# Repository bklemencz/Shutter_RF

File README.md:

STM8S103 mini board based shutter controller

- 433MHz EV1527 based remote control
- RS485 Intarface
- IIC interface and RF transmitter on board
- 2 relays for 3 wire tubular shutter motors
- External switch
- Time based partially open and closed positions

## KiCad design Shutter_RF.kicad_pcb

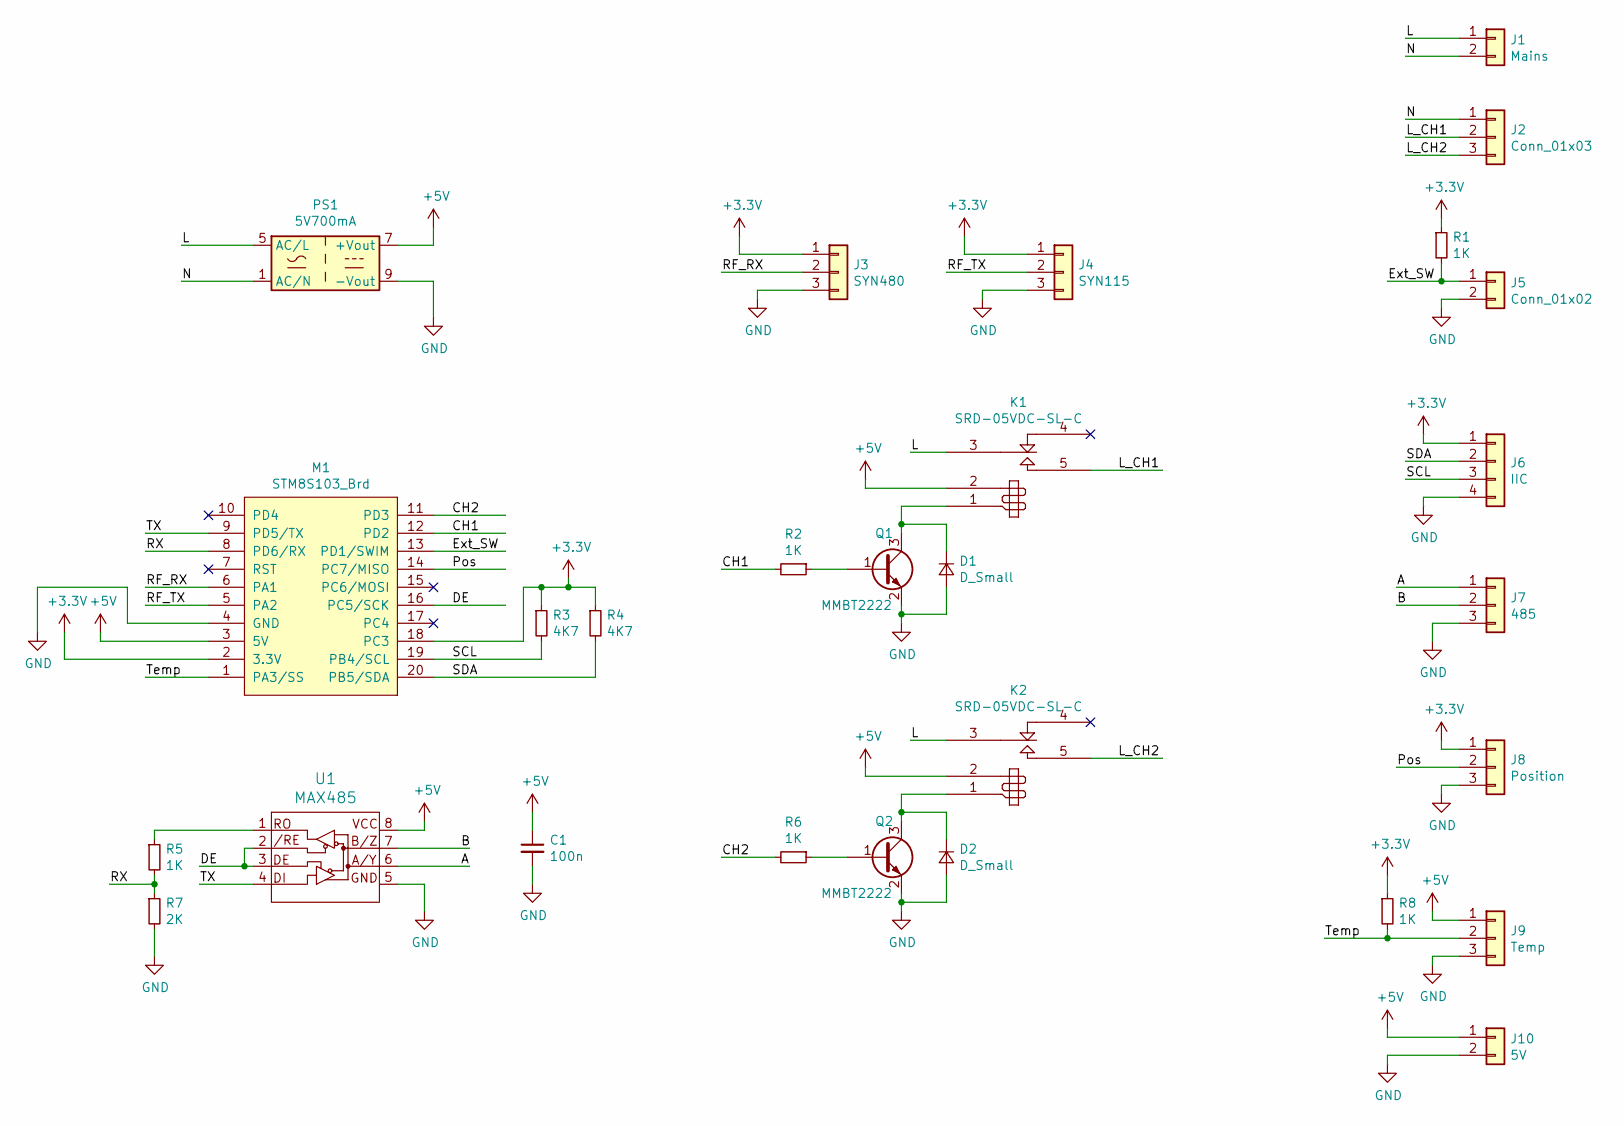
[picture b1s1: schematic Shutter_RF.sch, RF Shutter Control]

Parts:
C1: 100n; C_0805
D1, D2: D_Small; D_SMA
J1: Mains; Screw_Terminal_1x02
J2: Conn_01x03; Screw_Terminal_1x03
J3: SYN480; SYN480R_Mod
J4: SYN115; SYN115_Mod
J5: Conn_01x02; Screw_Terminal_1x02
J6: IIC; JST_PH_B4B-PH-K_04x2.00mm_Straight
J7: 485; JST_PH_B3B-PH-K_03x2.00mm_Straight
J8: Position; JST_PH_B3B-PH-K_03x2.00mm_Straight
J9: Temp; JST_PH_B3B-PH-K_03x2.00mm_Straight
J10: 5V; Screw_Terminal_1x02
K1, K2: SRD-05VDC-SL-C; REY5-19.0X15.0X15.0MM
M1: STM8S103_Brd; STM8S103_Minimum_Board
PS1: 5V700mA; 5V700mA_ACDC
Q1, Q2: MMBT2222; SOT-23
R1, R2, R5, R6, R8: 1K; R_0805
R3, R4: 4K7; R_0805
R7: 2K; R_0805
U1: MAX485; SOIC-8_3.9x4.9mm_Pitch1.27mm

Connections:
+3V3: J3.1, J4.1, J6.1, J8.1, M1.2 (3.3V), M1.18 (PC3), R1.1, R3.1, R4.1, R8.1
+5V: C1.1, J9.1, J10.1, K1.2, K2.2, M1.3 (5V), PS1.7 (+Vout), U1.8 (VCC)
/A: J7.1, U1.6 (A/Y)
/B: J7.2, U1.7 (B/Z)
/CH1: M1.12 (PD2), R2.2
/CH2: M1.11 (PD3), R6.2
/DE: M1.16 (PC5/SCK), U1.2 (/RE), U1.3 (DE)
/Ext_SW: J5.1, M1.13 (PD1/SWIM), R1.2
/L: J1.1, K1.3, K2.3, PS1.5 (AC/L)
/L_CH1: J2.2, K1.5
/L_CH2: J2.3, K2.5
/N: J1.2, J2.1, PS1.1 (AC/N)
/Pos: J8.2, M1.14 (PC7/MISO)
/RF_RX: J3.2, M1.6 (PA1)
/RF_TX: J4.2, M1.5 (PA2)
/RX: M1.8 (PD6/RX), R5.2, R7.1
/SCL: J6.3, M1.19 (PB4/SCL), R3.2
/SDA: J6.2, M1.20 (PB5/SDA), R4.2
/TX: M1.9 (PD5/TX), U1.4 (DI)
/Temp: J9.2, M1.1 (PA3/SS), R8.2
GND: C1.2, D1.2 (A), D2.2 (A), J3.3, J4.3, J5.2, J6.4, J7.3, J8.3, J9.3, J10.2, M1.4 (GND), PS1.9 (-Vout), Q1.2 (E), Q2.2 (E), R7.2, U1.5 (GND)
unnamed: D1.1 (K), K1.1, Q1.3 (C)
unnamed: D2.1 (K), K2.1, Q2.3 (C)
unnamed: Q1.1 (B), R2.1
unnamed: Q2.1 (B), R6.1
unnamed: R5.1, U1.1 (RO)

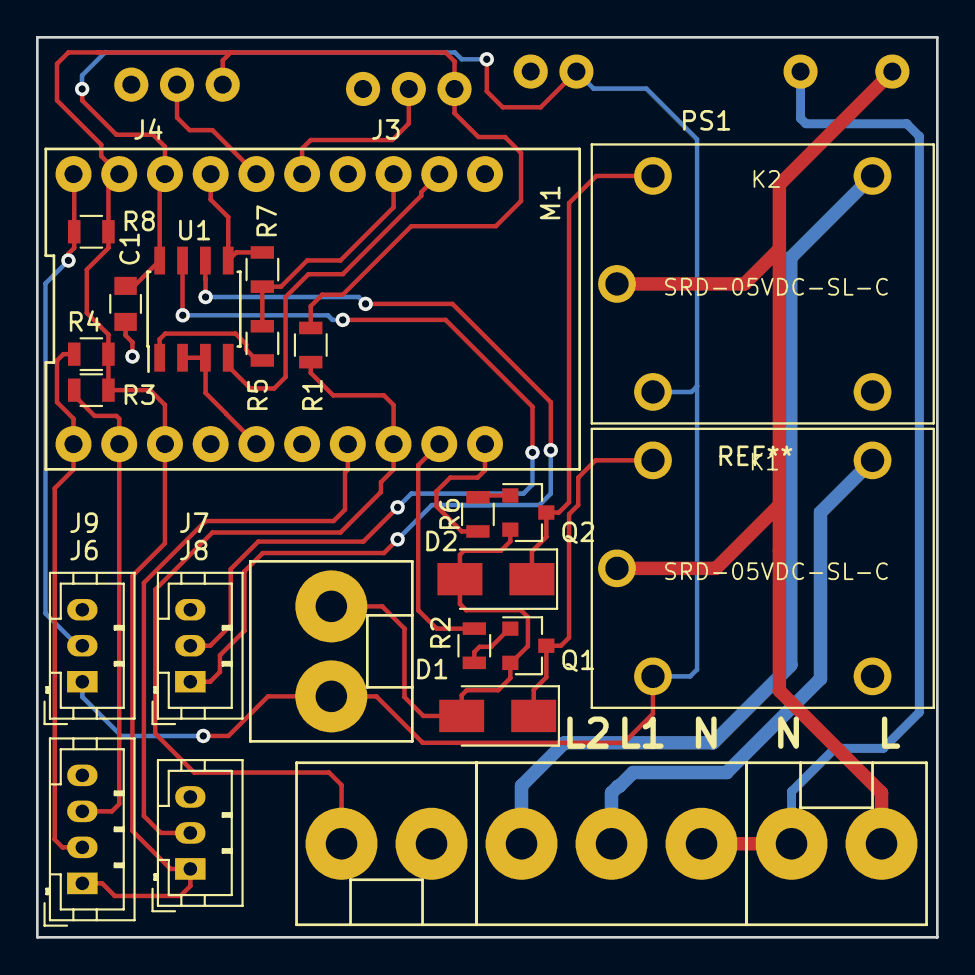
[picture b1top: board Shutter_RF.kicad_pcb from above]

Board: 2 copper layers, 50.0 x 50.0 mm, 28 parts (0 on the bottom side), 26 nets.

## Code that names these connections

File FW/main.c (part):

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
/*
PINOUT
PD1 - External Switch
PD2 - Relay CH1
PD3 - Relay CH2
PD5 - RS485_TX
PD6 - RS485_RX
PA1 - RF_RX
PA2 - RF_TX
PA3 - TEMPERATURE
PB4 - I2C_SCL
PB5 - I2C_SDA
PC3 - INPUT_VDD3.3V
PC5 - RS485_DE
PC7 - POSITION

FEATURES:
SHUTTER
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	CLK_SYSCLKConfig(CLK_PRESCALER_CPUDIV1);
	FLASH_DeInit();
	GPIO_DeInit(GPIOA);
	GPIO_Init(GPIOA,GPIO_PIN_1,GPIO_MODE_IN_PU_IT);			//RF_RX
	GPIO_Init(GPIOA,GPIO_PIN_2,GPIO_MODE_OUT_PP_LOW_FAST);	//RF_TX
	GPIO_DeInit(GPIOC);
	GPIO_Init(GPIOC,GPIO_PIN_3,GPIO_MODE_IN_FL_NO_IT);		//VDD
	GPIO_Init(GPIOC,GPIO_PIN_5,GPIO_MODE_OUT_PP_LOW_FAST);	//RS485_DE
	GPIO_WriteLow(GPIOC,GPIO_PIN_5);						// Serial RX enable
	GPIO_Init(GPIOC,GPIO_PIN_7,GPIO_MODE_IN_PU_IT);			//POSITION
	GPIO_DeInit(GPIOD);
	GPIO_Init(GPIOD,GPIO_PIN_1,GPIO_MODE_IN_PU_NO_IT);			//EXT_SW
	GPIO_Init(GPIOD,GPIO_PIN_4,GPIO_MODE_IN_PU_NO_IT);
	GPIO_Init(GPIOD,GPIO_PIN_2,GPIO_MODE_OUT_PP_LOW_FAST);	//Relay1
	GPIO_Init(GPIOD,GPIO_PIN_3,GPIO_MODE_OUT_PP_LOW_FAST);	//Relay2
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
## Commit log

2019-12-02 Initial
2019-12-06 FW_Project_Init
2019-12-06 interrupt vectors
2019-12-11 Basic functions done
2019-12-11 Remove Gerber Files
2020-01-10 Working Code
    Not Cleaned up yet
2020-01-11 RF Transmission added
2020-12-04 Ext Switch
2020-12-04 Common Folder
2020-12-08 v2.0 485 protocol changed
2020-12-08 v2.01 Relay Control Deadtime
